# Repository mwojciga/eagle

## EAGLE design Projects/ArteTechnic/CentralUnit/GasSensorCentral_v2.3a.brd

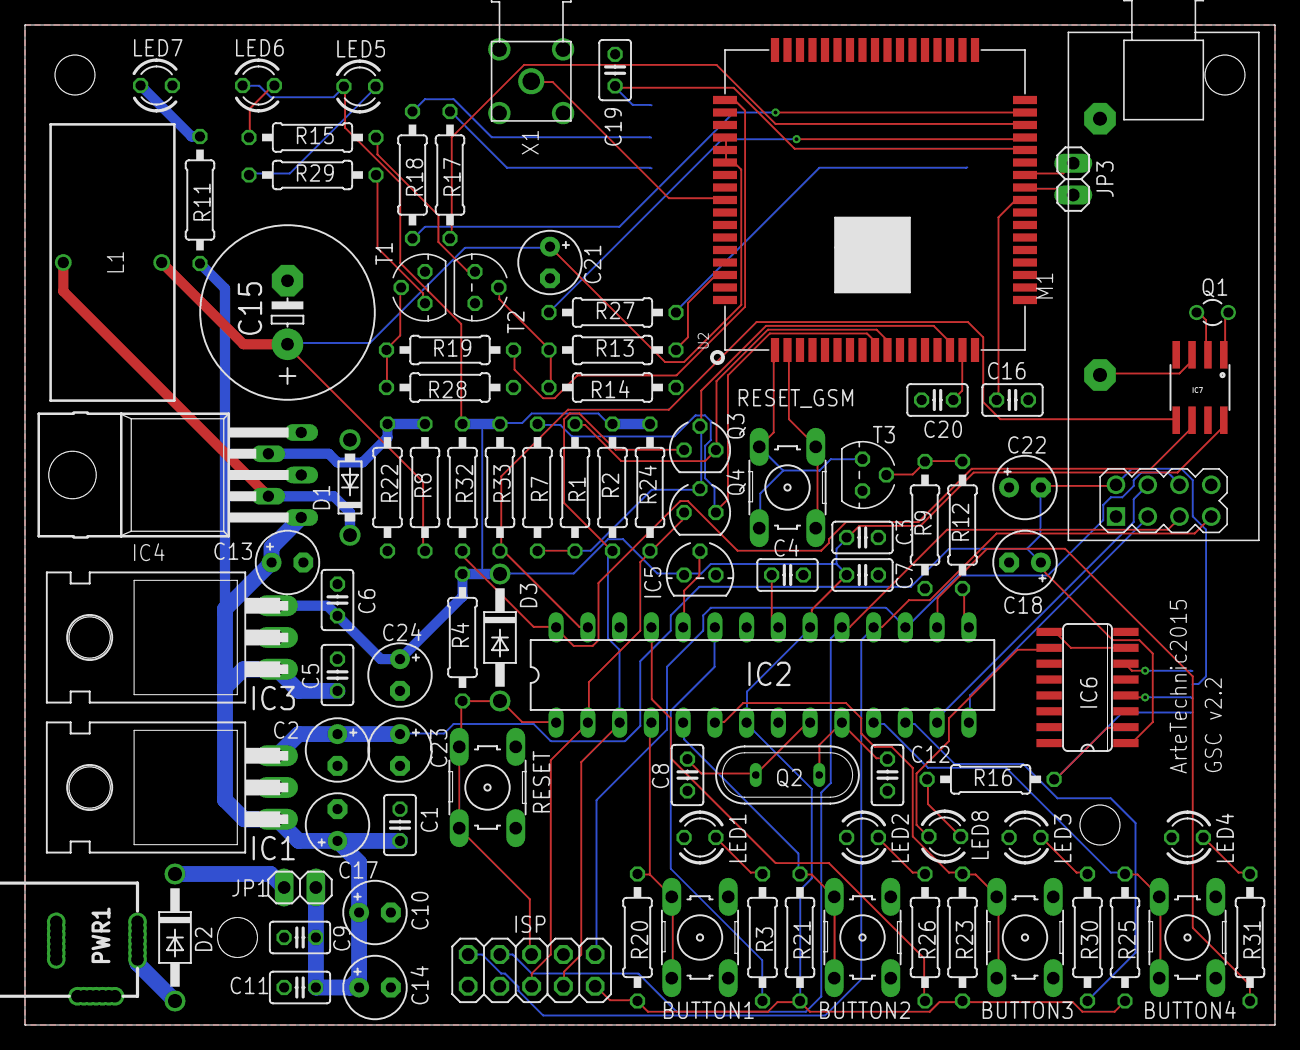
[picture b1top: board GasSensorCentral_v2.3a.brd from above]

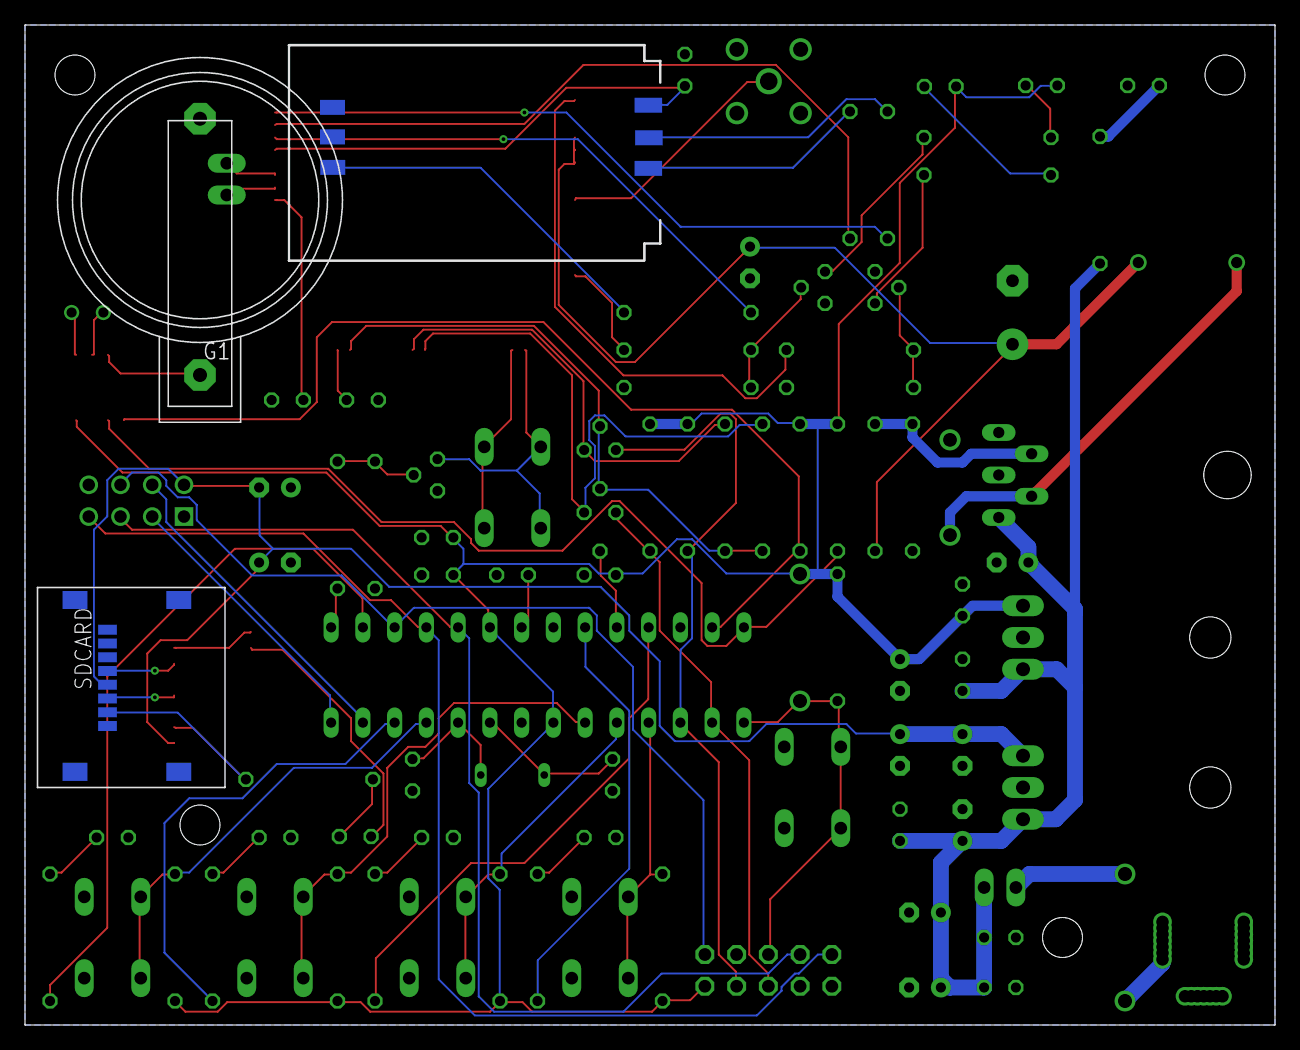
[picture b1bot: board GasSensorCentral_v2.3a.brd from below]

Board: 2 copper layers, 100.0 x 80.0 mm, 96 parts (3 on the bottom side), 72 nets.

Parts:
BUTTON1, BUTTON2, BUTTON3, BUTTON4: B3F-10XX
C1, C3, C4, C6, C7, C9, C11, C19, C20: 100nF; C025-025X050
C2: 2.2uF; E2,5-5
C5: 330nF; C025-025X050
C8, C12: 22pF; C025-025X050
C10, C17, C22, C23, C24: 1uF; E2,5-5
C13, C21: 100uF; E2,5-5
C14: 4.7uF; E2,5-5
C15: 3300uF; E5-13
C16: 4.7uF; C025-025X050
C18: 10uF; E2,5-5
D1: 1N5823; DO41-7.6
D2, D3: 1N4001; DO41-10
G1: CR2032H
IC1: LF33CV; TO220H
IC2: MEGA8-P; DIL28-3
IC3: 7805T; TO220H
IC4: LM2576H; TO220-52
IC5: LM35CZ; TO92
IC6: 4050D; SO16
IC7: DS1307SO8; SO08
ISP: 2X05
JP1, JP3: 1X02
L1: 68uH; TJ4-U1
LED1, LED2, LED3, LED4: White; LED3MM
LED5, LED6, LED7: Blue; LED3MM
LED8: Yellow; LED3MM
M1: NRF24L01; WIRELESS-NRD24L01-PA-EXT
PWR1: PWR_JACK_UNI_MILLING
Q1: 32.768K-20PPM; TC26V
Q2: QS
Q3, Q4: BS170; SOT54E
R1, R2, R7, R11, R20, R21, R23, R24, R25, R32, R33: 10k; 0207/10
R3, R15, R26, R29, R30, R31: 330; 0207/10
R4: 22k; 0207/10
R8: 3.6k; 0207/10
R9, R14, R28: 47k; 0207/10
R12, R13, R19: 4.7k; 0207/10
R16: 1k; 0207/10
R17, R18, R27: 22R; 0207/10
R22: 1.5k; 0207/10
RESET: B3F-10XX
RESET_GSM: B3F-10XX
SDCARD: MX-47219-2001
SIMHOLDER: SIMHOLDER3
T1, T2, T3: BC547; TO92
U2: SIM900
X1: BU-SMA-G

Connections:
3V3: C2.+, C18.+, C22.-, C23.+, IC1.3, IC6.1, M1.2, SDCARD.4
5V0: C3.1, C6.1, C7.1, C24.+, D3.C, IC2.7, IC2.20, IC3.3, IC5.1, IC7.8, ISP.2, LED5.A, LED6.A, R2.2, R4.2, R20.2, R21.2, R23.2, R24.2, R25.2, R32.1, R33.1
BUTTON1: BUTTON1.3, BUTTON1.4, IC2.4, R20.1
BUTTON2: BUTTON2.3, BUTTON2.4, IC2.5, R21.1
BUTTON3: BUTTON3.3, BUTTON3.4, IC2.6, R23.1
BUTTON4: BUTTON4.3, BUTTON4.4, IC2.11, R25.1
CE: IC2.14, M1.3
CSN: IC2.13, M1.4
DBG_RXD: JP3.2, U2.28
DBG_TXD: JP3.1, U2.27
GND: BUTTON1.1, BUTTON1.2, BUTTON2.1, BUTTON2.2, BUTTON3.1, BUTTON3.2, BUTTON4.1, BUTTON4.2, C1.2, C2.-, C3.2, C4.2, C5.2, C6.2, C7.2, C8.1, C9.1, C10.-, C11.1, C12.1, C13.-, C14.-, C15.-, C16.1, C17.-, C18.-, C19.2, C20.1, C21.-, C22.+, C23.-, C24.-, D1.A, G1.-, IC1.2, IC2.8, IC2.22, IC3.2, IC4.3, IC4.5, IC5.3, IC6.8, IC6.11, IC6.14, IC7.4, ISP.3, ISP.8, ISP.10, LED1.K, LED2.K, LED3.K, LED4.K, LED7.K, M1.1, PWR1.-, PWR1.--, R9.1, R14.1, R22.2, R28.1, RESET.1, RESET.2, SDCARD.6, SDCARD.G1, SDCARD.G2, SDCARD.G3, SDCARD.G4, SIMHOLDER.6, T1.1, T2.1, T3.1, U2.17, U2.18, U2.29, U2.39, U2.45, U2.46, U2.53, U2.54, U2.58, U2.59, U2.61, U2.62, U2.63, U2.64, U2.65, X1.2, X1.3, X1.4, X1.5
LED1: IC2.23, R3.2
LED2: IC2.25, R26.2
LED3: IC2.12, R30.2
LED4: IC2.16, R31.2
LRXD: Q3.S, R1.1, U2.10
LTXD: Q4.S, R7.1, U2.9
MISO: IC2.18, ISP.9, M1.7
MOSI: IC2.17, ISP.1, M1.6
unnamed: C4.1, IC2.21
unnamed: IC7.2, Q1.1
unnamed: IC4.4, R8.2, R22.1
unnamed: D2.A, PWR1.+
unnamed: LED1.A, R3.1
unnamed: R27.2, SIMHOLDER.4
unnamed: LED5.K, R29.1
unnamed: IC7.1, Q1.2
unnamed: R13.1, R14.2, T2.2
unnamed: LED7.A, R11.1
unnamed: LED6.K, R15.1
unnamed: D1.C, IC4.2, L1.1
unnamed: C20.2, U2.16
unnamed: R9.2, R12.2, T3.2
unnamed: R19.1, R28.2, T1.2
unnamed: G1.+, IC7.3
unnamed: C16.2, U2.26
unnamed: LED2.A, R26.1
unnamed: LED3.A, R30.1
unnamed: LED4.A, R31.1
unnamed: R18.1, SIMHOLDER.2
unnamed: R17.1, SIMHOLDER.3
unnamed: IC6.2, R16.2, SDCARD.2
unnamed: IC6.4, SDCARD.3
unnamed: C8.2, IC2.9, Q2.1
unnamed: IC6.6, SDCARD.5
unnamed: IC6.10, LED8.A
unnamed: LED8.K, R16.1
unnamed: C12.2, IC2.10, Q2.2
NETLIGHT: R19.2, U2.52
NETLIGHT_INFO: R29.2, T1.3
PWRKEY: RESET_GSM.3, RESET_GSM.4, T3.3, U2.1
PWRKEY_OUT: RESET_GSM.1, RESET_GSM.2, U2.2
RESET: D3.A, IC2.1, ISP.5, R4.1, RESET.3, RESET.4
RF_ANT: U2.60, X1.1
RXD: IC2.2, ISP.6, Q4.D, R24.1
SCK: IC2.19, ISP.7, M1.5
SCL: IC2.28, IC7.6, R32.2
SCLK: IC6.7, IC6.9
SDA: IC2.27, IC7.5, R33.2
SIM_CLK: R17.2, U2.32
SIM_DATA: R27.1, U2.31
SIM_RST: R18.2, U2.33
SIM_VDD: C19.1, SIMHOLDER.1, U2.30
SOFTRESET: IC2.15, R12.1
STATUS: R13.2, U2.66
STATUS_INFO: R15.2, T2.3
TEMP: IC2.24, IC5.2
TXD: IC2.3, ISP.4, Q3.D, R2.1
VBAT: C15.+, C21.+, L1.2, R8.1, U2.55, U2.56, U2.57
VDD_EXT: Q3.G, Q4.G, R1.2, R7.2, U2.15
VIN_BUTTON: C1.1, C5.1, C9.2, C10.+, C11.2, C13.+, C14.+, C17.+, IC1.1, IC3.1, IC4.1, JP1.2, R11.2
VIN_JACK: D2.C, JP1.1

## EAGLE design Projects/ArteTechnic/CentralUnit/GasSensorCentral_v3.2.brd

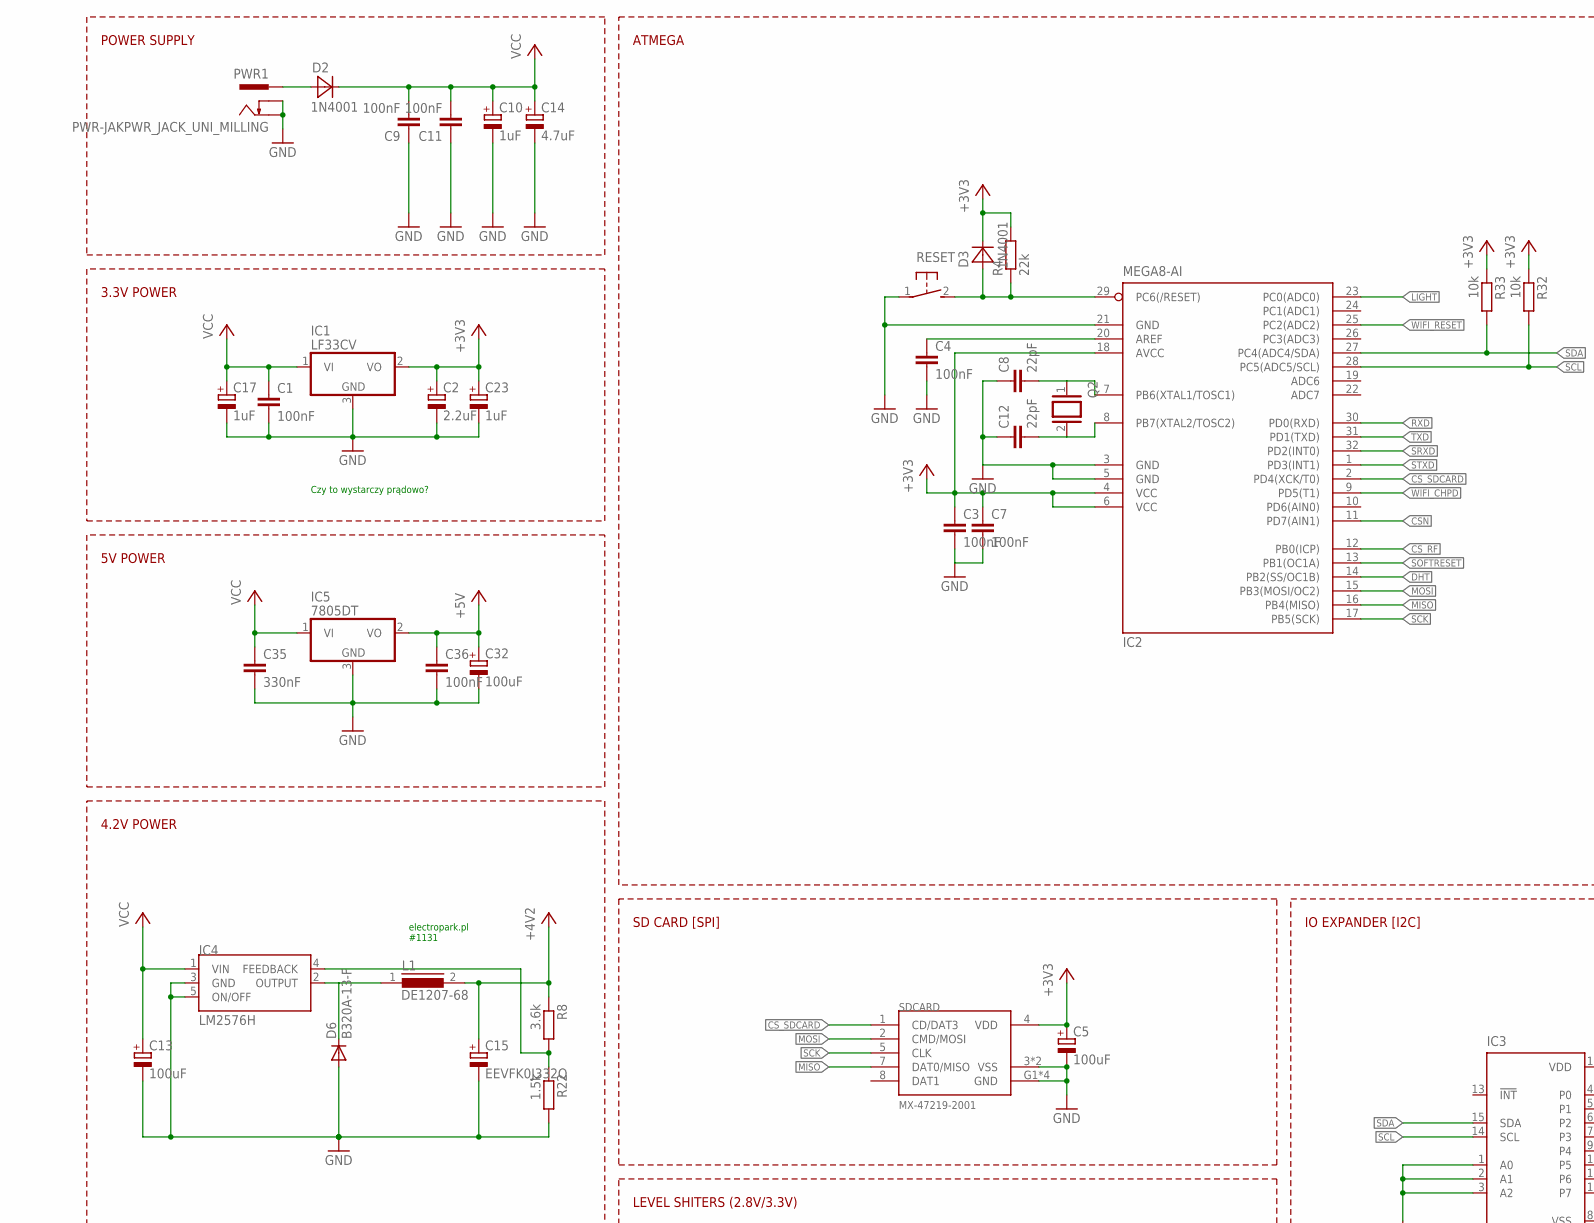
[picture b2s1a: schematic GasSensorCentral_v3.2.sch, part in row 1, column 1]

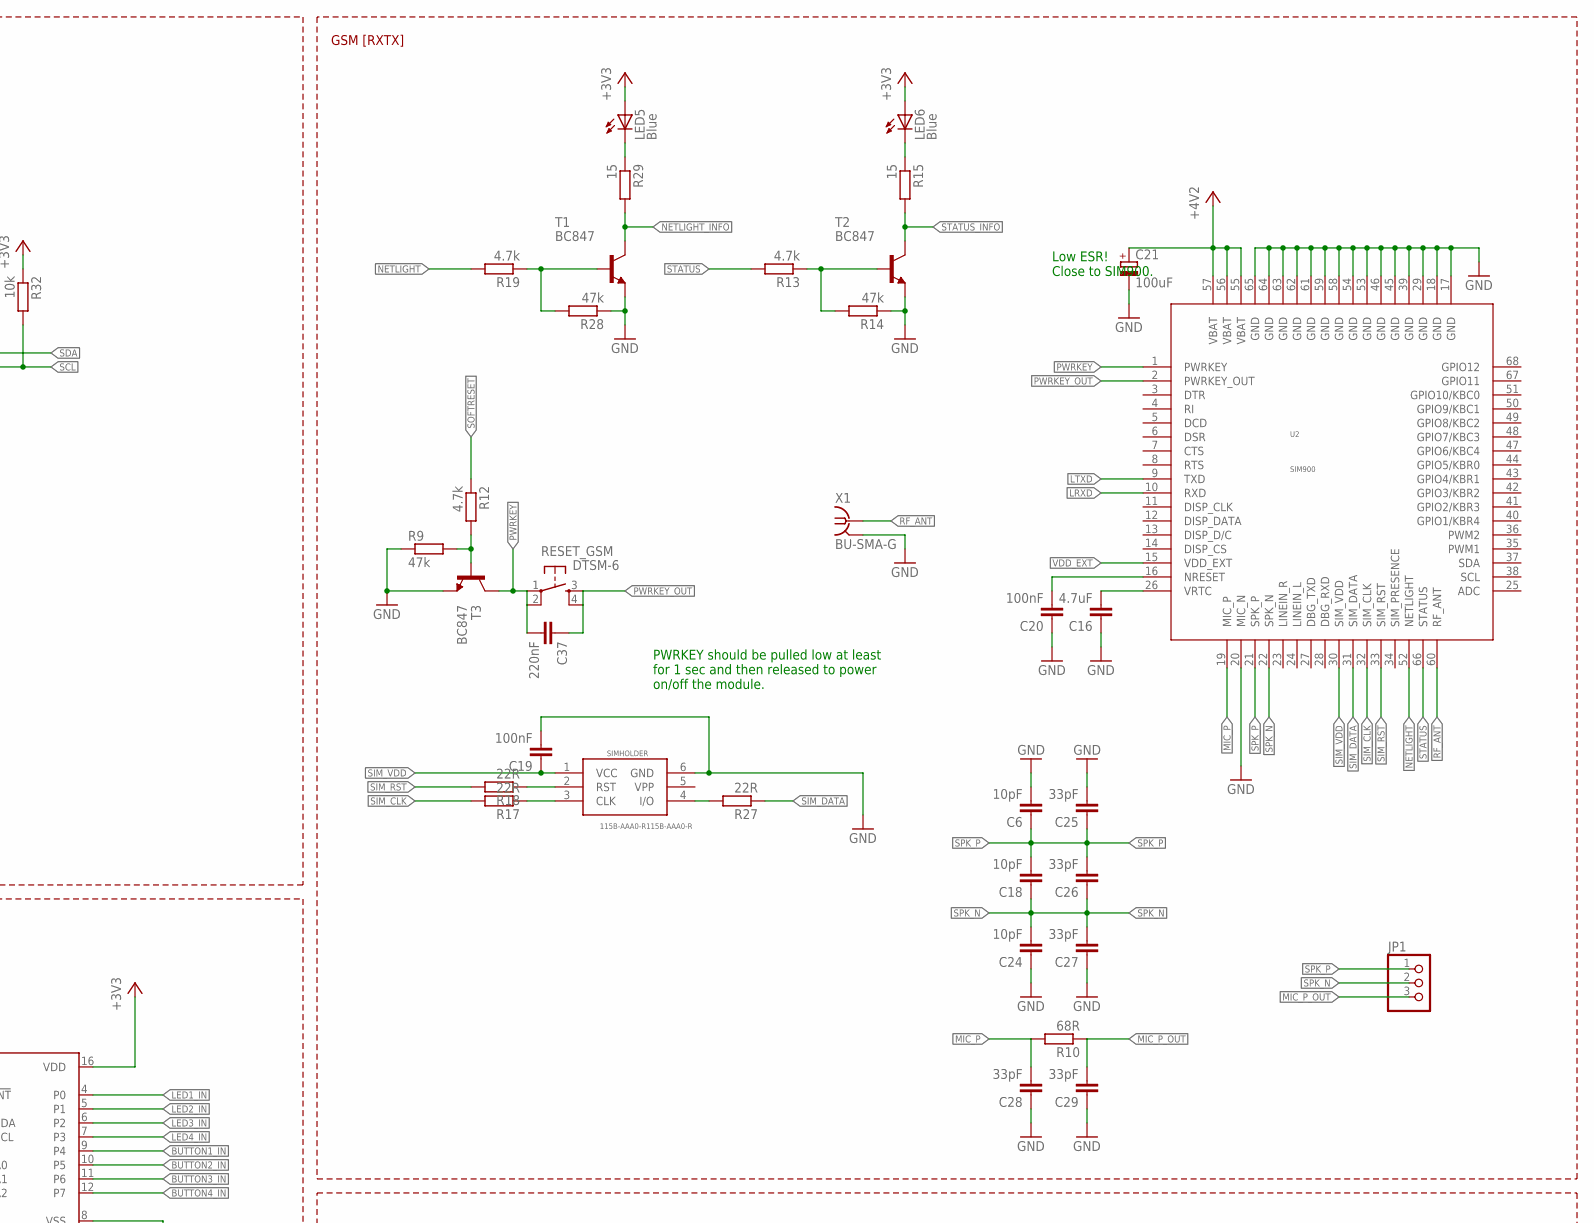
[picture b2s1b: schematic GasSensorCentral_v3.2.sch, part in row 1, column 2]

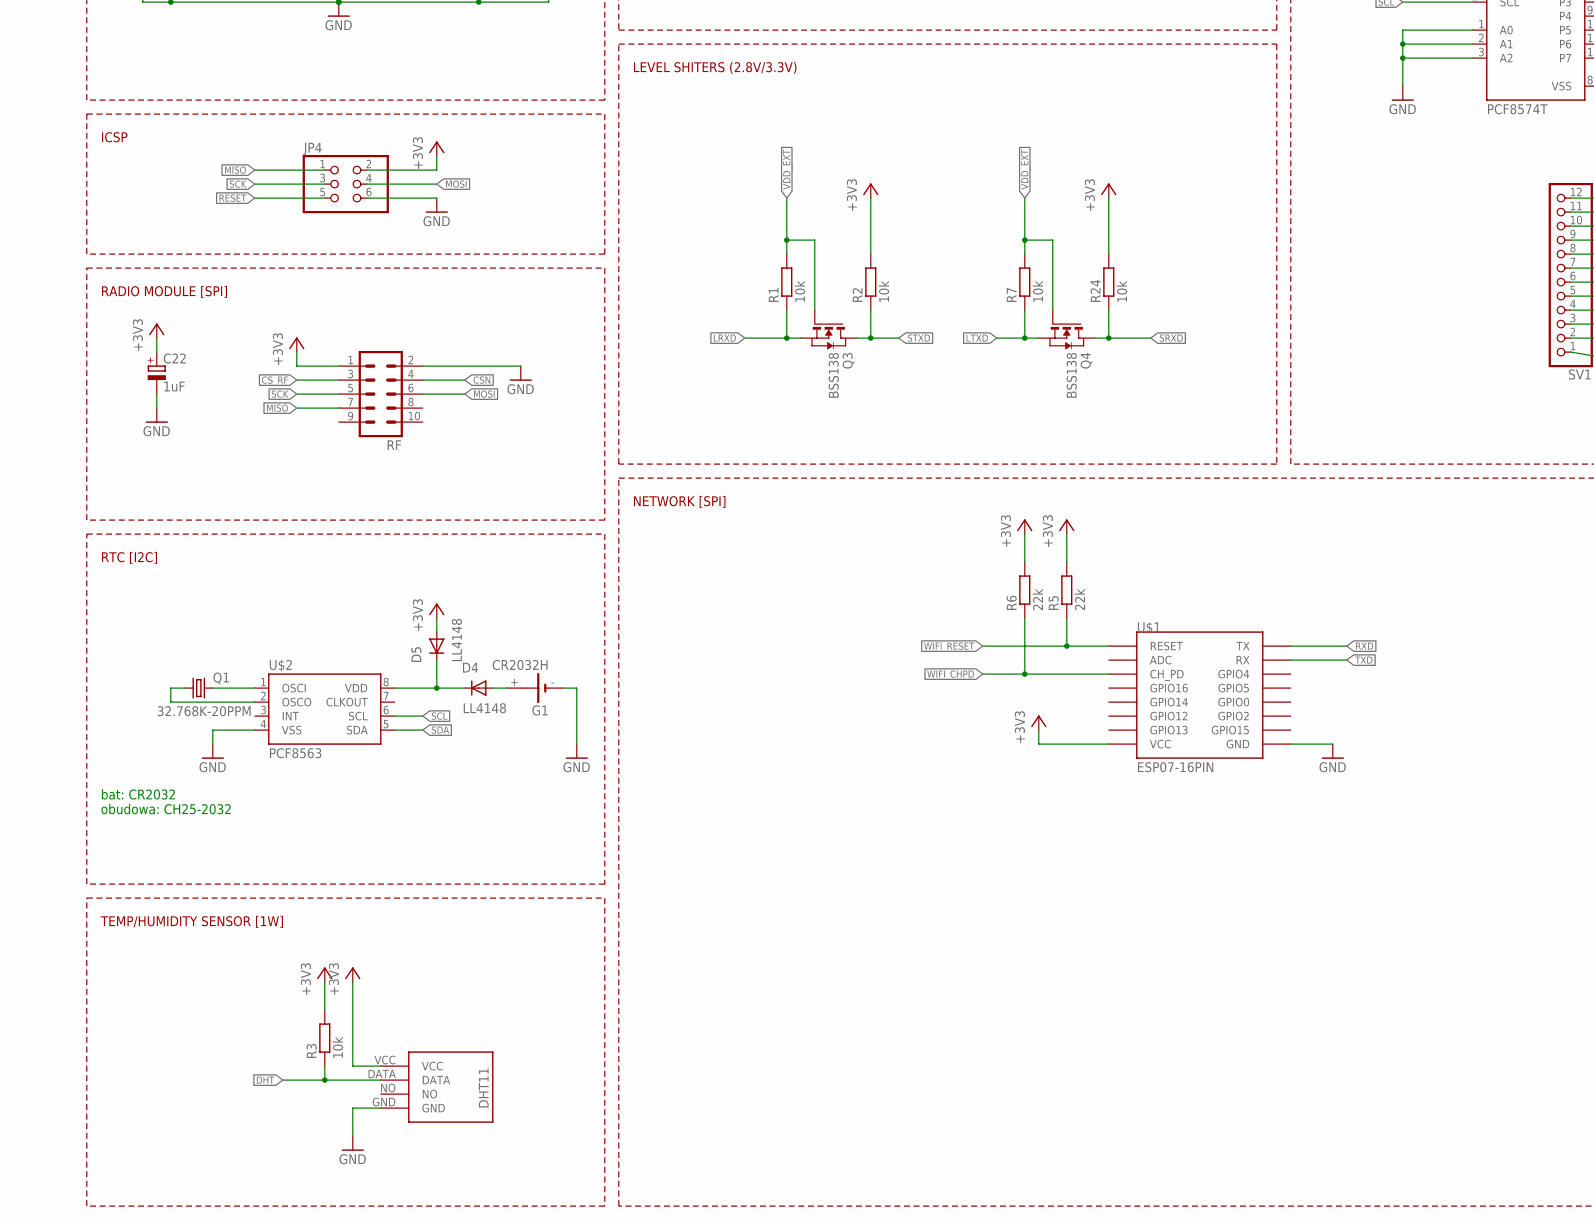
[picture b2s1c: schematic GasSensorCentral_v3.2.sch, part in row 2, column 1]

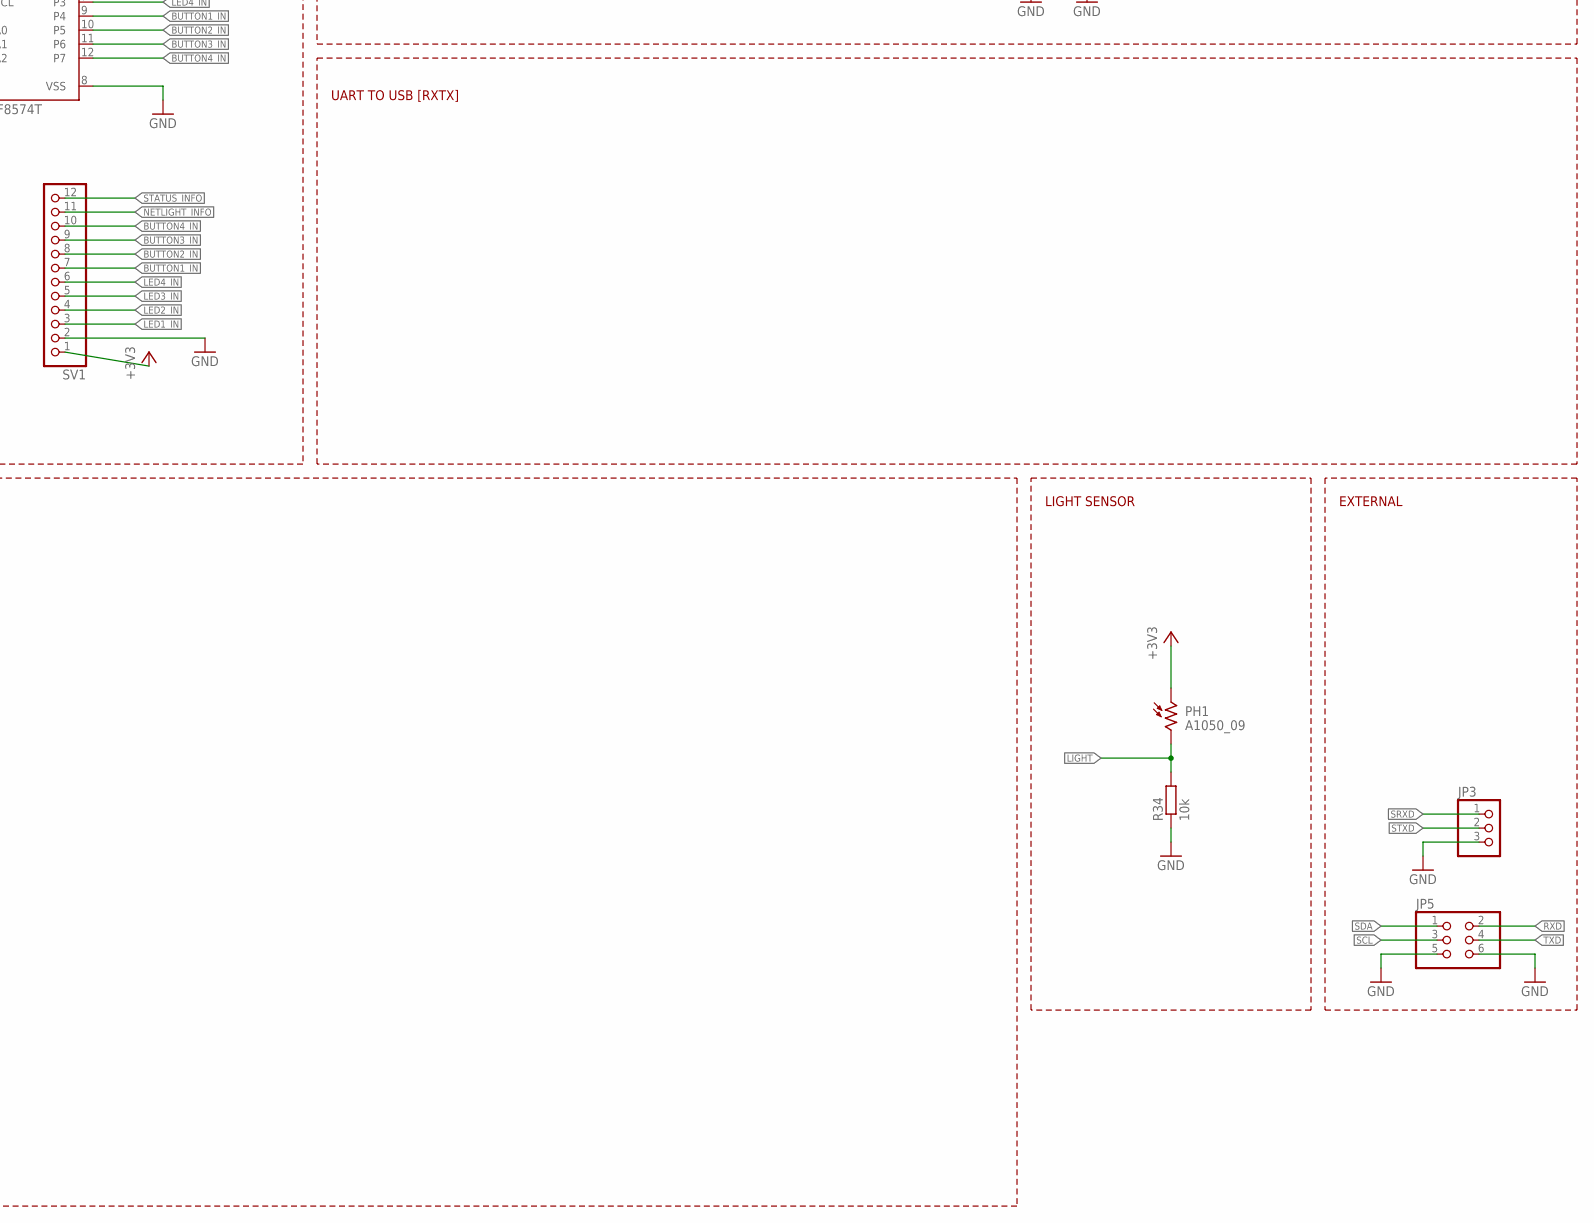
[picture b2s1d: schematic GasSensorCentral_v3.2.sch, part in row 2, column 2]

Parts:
C1, C3, C4, C7, C9, C11, C19, C20, C36: 100nF; C0805
C2: 2.2uF; PANASONIC_B
C5, C13, C21, C32: 100uF; PANASONIC_B
C6, C18, C24: 10pF; C0805
C8, C12: 22pF; C0805
C10, C17, C22, C23: 1uF; PANASONIC_B
C14: 4.7uF; PANASONIC_B
C15: EEVFK0J332Q; 153CLV-1212
C16: 4.7uF; C0805
C25, C26, C27, C28, C29: 33pF; C0805
C35: 330nF; C0805
C37: 220nF; C0805
D2, D3: 1N4001; SMA
D4, D5: LL4148; SOD80C
D6: B320A-13-F; DO214AC
G1: CR2032H
IC1: LF33CV; TO252
IC2: MEGA8-AI; TQFP32-08
IC3: PCF8574T; SO16W
IC4: LM2576H; TO220-52
IC5: 7805DT; TO252
JP1: PINHD-1X3/90; 1X03/90
JP3: PINHD-1X3; 1X03
JP4, JP5: PINHD-2X3; 2X03
L1: DE1207-68; DE1207
LED5, LED6: Blue; SML0805
PH1: A1050_09; T0-46-A10XX
PWR1: PWR-JAKPWR_JACK_UNI_MILLING; PWR_JACK_UNI_MILLING
Q1: 32.768K-20PPM; TC26V
Q2: XTAL/S; QS
Q3, Q4: BSS138; SOT-23
R1, R2, R3, R7, R24, R32, R33, R34: 10k; R0805
R4, R5, R6: 22k; R0805
R8: 3.6k; R0805
R9, R14, R28: 47k; R0805
R10: 68R; R0805
R12, R13, R19: 4.7k; R0805
R15, R29: 15; R0805
R17, R18, R27: 22R; R0805
R22: 1.5k; R0805
RESET: 31-XX; B3F-31XX
RESET_GSM: DTSM-6
RF: ML10
SDCARD: MX-47219-2001
SIMHOLDER: 115B-AAA0-R115B-AAA0-R; 115B-AAA0-R
SV1: PINHD-1X12; 1X12
T1, T2, T3: BC847; SOT23
U2: SIM900
U$1: ESP07-16PIN
U$2: PCF8563; SO08
U$3: DHT11-PION.
X1: BU-SMA-G

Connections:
+3V3: C2.+, C3.1, C5.+, C7.1, C22.+, C23.+, D3.C, D5.A, IC1.2 (VO), IC2.4 (VCC), IC2.6 (VCC), IC2.18 (AVCC), IC3.16 (VDD), JP4.2, LED5.A, LED6.A, PH1.1, R2.2, R3.2, R4.2, R5.2, R6.2, R24.2, R32.1, R33.1, RF.1, SDCARD.4 (VDD), SV1.1, U$1.VCC, U$3.VCC
+4V2: C15.+, C21.+, L1.2, R8.1, U2.55 (VBAT), U2.56 (VBAT), U2.57 (VBAT)
+5V: C32.+, C36.1, IC5.2 (VO)
BUTTON1_IN: IC3.9 (P4), SV1.7
BUTTON2_IN: IC3.10 (P5), SV1.8
BUTTON3_IN: IC3.11 (P6), SV1.9
BUTTON4_IN: IC3.12 (P7), SV1.10
CSN: IC2.11 (PD7(AIN1)), RF.4
CS_RF: IC2.12 (PB0(ICP)), RF.3
CS_SDCARD: IC2.2 (PD4(XCK/T0)), SDCARD.1 (CD/DAT3)
DHT: IC2.14 (PB2(SS/OC1B)), R3.1, U$3.DATA
GND: C1.2, C2.-, C3.2, C4.2, C5.-, C6.2, C7.2, C8.1, C9.1, C10.-, C11.1, C12.1, C13.-, C14.-, C15.-, C16.1, C17.-, C19.2, C20.1, C21.-, C22.-, C23.-, C24.1, C25.2, C27.1, C28.1, C29.1, C32.-, C35.2, C36.2, G1.-, IC1.3 (GND), IC2.3 (GND), IC2.5 (GND), IC2.21 (GND), IC3.1 (A0), IC3.2 (A1), IC3.3 (A2), IC3.8 (VSS), IC4.3 (GND), IC4.5 (ON/OFF), IC5.3 (GND), JP3.3, JP4.6, JP5.5, JP5.6, PWR1.-, PWR1.-1 (-), PWR1.-2 (-), PWR1.-3 (-), PWR1.-4 (-), PWR1.-5 (-), PWR1.-6 (-), PWR1.--, PWR1.--1 (--), PWR1.--2 (--), PWR1.--3 (--), PWR1.--4 (--), PWR1.--5 (--), PWR1.--6 (--), R9.1, R14.1, R22.2, R28.1, R34.1, RESET.1, RF.2, SDCARD.3 (VSS), SDCARD.6 (VSS), SDCARD.G1 (GND), SDCARD.G2 (GND), SDCARD.G3 (GND), SDCARD.G4 (GND), SIMHOLDER.6 (GND), SV1.2, T1.2 (E), T2.2 (E), T3.2 (E), U2.17 (GND), U2.18 (GND), U2.20 (MIC_N), U2.29 (GND), U2.39 (GND), U2.45 (GND), U2.46 (GND), U2.53 (GND), U2.54 (GND), U2.58 (GND), U2.59 (GND), U2.61 (GND), U2.62 (GND), U2.63 (GND), U2.64 (GND), U2.65 (GND), U$1.GND, U$2.4 (VSS), U$3.GND, X1.2, X1.3 (2), X1.4 (2), X1.5 (2)
LED1_IN: IC3.4 (P0), SV1.3
LED2_IN: IC3.5 (P1), SV1.4
LED3_IN: IC3.6 (P2), SV1.5
LED4_IN: IC3.7 (P3), SV1.6
LIGHT: IC2.23 (PC0(ADC0)), PH1.2, R34.2
LRXD: Q3.2 (S), R1.1, U2.10 (RXD)
LTXD: Q4.2 (S), R7.1, U2.9 (TXD)
MIC_P: C28.2, R10.2, U2.19 (MIC_P)
MIC_P_OUT: C29.2, JP1.3, R10.1
MISO: IC2.16 (PB4(MISO)), JP4.1, RF.7, SDCARD.7 (DAT0/MISO)
MOSI: IC2.15 (PB3(MOSI/OC2)), JP4.4, RF.6, SDCARD.2 (CMD/MOSI)
unnamed: C4.1, IC2.20 (AREF)
unnamed: Q1.1, U$2.2 (OSCO)
unnamed: IC4.4 (FEEDBACK), R8.2, R22.1
unnamed: D2.A, PWR1.+, PWR1.+1 (+), PWR1.+2 (+), PWR1.+3 (+), PWR1.+4 (+), PWR1.+5 (+), PWR1.+6 (+)
unnamed: D4.C, D5.C, U$2.8 (VDD)
unnamed: R27.2, SIMHOLDER.4 (I/O)
unnamed: LED5.C, R29.1
unnamed: Q1.2, U$2.1 (OSCI)
unnamed: R13.1, R14.2, T2.1 (B)
unnamed: LED6.C, R15.1
unnamed: D6.C, IC4.2 (OUTPUT), L1.1
unnamed: C20.2, U2.16 (NRESET)
unnamed: R9.2, R12.2, T3.1 (B)
unnamed: R19.1, R28.2, T1.1 (B)
unnamed: D4.A, G1.+
unnamed: C16.2, U2.26 (VRTC)
unnamed: R18.1, SIMHOLDER.2 (RST)
unnamed: R17.1, SIMHOLDER.3 (CLK)
unnamed: C8.2, IC2.7 (PB6(XTAL1/TOSC1)), Q2.1
unnamed: C12.2, IC2.8 (PB7(XTAL2/TOSC2)), Q2.2
NETLIGHT: R19.2, U2.52 (NETLIGHT)
NETLIGHT_INFO: R29.2, SV1.11, T1.3 (C)
PWRKEY: C37.2, RESET_GSM.1, RESET_GSM.2, T3.3 (C), U2.1 (PWRKEY)
PWRKEY_OUT: C37.1, RESET_GSM.3, RESET_GSM.4, U2.2 (PWRKEY_OUT)
RESET: D3.A, IC2.29 (PC6(/RESET)), JP4.5, R4.1, RESET.2 (S)
RF_ANT: U2.60 (RF_ANT), X1.1
RXD: IC2.30 (PD0(RXD)), JP5.2, U$1.TX
SCK: IC2.17 (PB5(SCK)), JP4.3, RF.5, SDCARD.5 (CLK)
SCL: IC2.28 (PC5(ADC5/SCL)), IC3.14 (SCL), JP5.3, R32.2, U$2.6 (SCL)
SDA: IC2.27 (PC4(ADC4/SDA)), IC3.15 (SDA), JP5.1, R33.2, U$2.5 (SDA)
SIM_CLK: R17.2, U2.32 (SIM_CLK)
SIM_DATA: R27.1, U2.31 (SIM_DATA)
SIM_RST: R18.2, U2.33 (SIM_RST)
SIM_VDD: C19.1, SIMHOLDER.1 (VCC), U2.30 (SIM_VDD)
SOFTRESET: IC2.13 (PB1(OC1A)), R12.1
SPK_N: C18.1, C24.2, C26.1, C27.2, JP1.2, U2.22 (SPK_N)
SPK_P: C6.1, C18.2, C25.1, C26.2, JP1.1, U2.21 (SPK_P)
SRXD: IC2.32 (PD2(INT0)), JP3.1, Q4.1 (D), R24.1
STATUS: R13.2, U2.66 (STATUS)
STATUS_INFO: R15.2, SV1.12, T2.3 (C)
STXD: IC2.1 (PD3(INT1)), JP3.2, Q3.1 (D), R2.1
TXD: IC2.31 (PD1(TXD)), JP5.4, U$1.RX
VCC: C1.1, C9.2, C10.+, C11.2, C13.+, C14.+, C17.+, C35.1, D2.C, IC1.1 (VI), IC4.1 (VIN), IC5.1 (VI)
VDD_EXT: Q3.3 (G), Q4.3 (G), R1.2, R7.2, U2.15 (VDD_EXT)
WIFI_CHPD: IC2.9 (PD5(T1)), R6.1, U$1.CH_PD
WIFI_RESET: IC2.25 (PC2(ADC2)), R5.1, U$1.REST (RESET)

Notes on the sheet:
PWRKEY should be pulled low at least for 1 sec and then released to power on/off the module.
Low ESR! Close to SIM900.
bat: CR2032 obudowa: CH25-2032
POWER SUPPLY
3.3V POWER
ICSP
4.2V POWER
RADIO MODULE [SPI]
LEVEL SHITERS (2.8V/3.3V)
ATMEGA
SD CARD [SPI]
RTC [I2C]
GSM [RXTX]
NETWORK [SPI]
IO EXPANDER [I2C]
TEMP/HUMIDITY SENSOR [1W]
electropark.pl #1131
UART TO USB [RXTX]
LIGHT SENSOR
EXTERNAL
5V POWER
Czy to wystarczy prądowo?

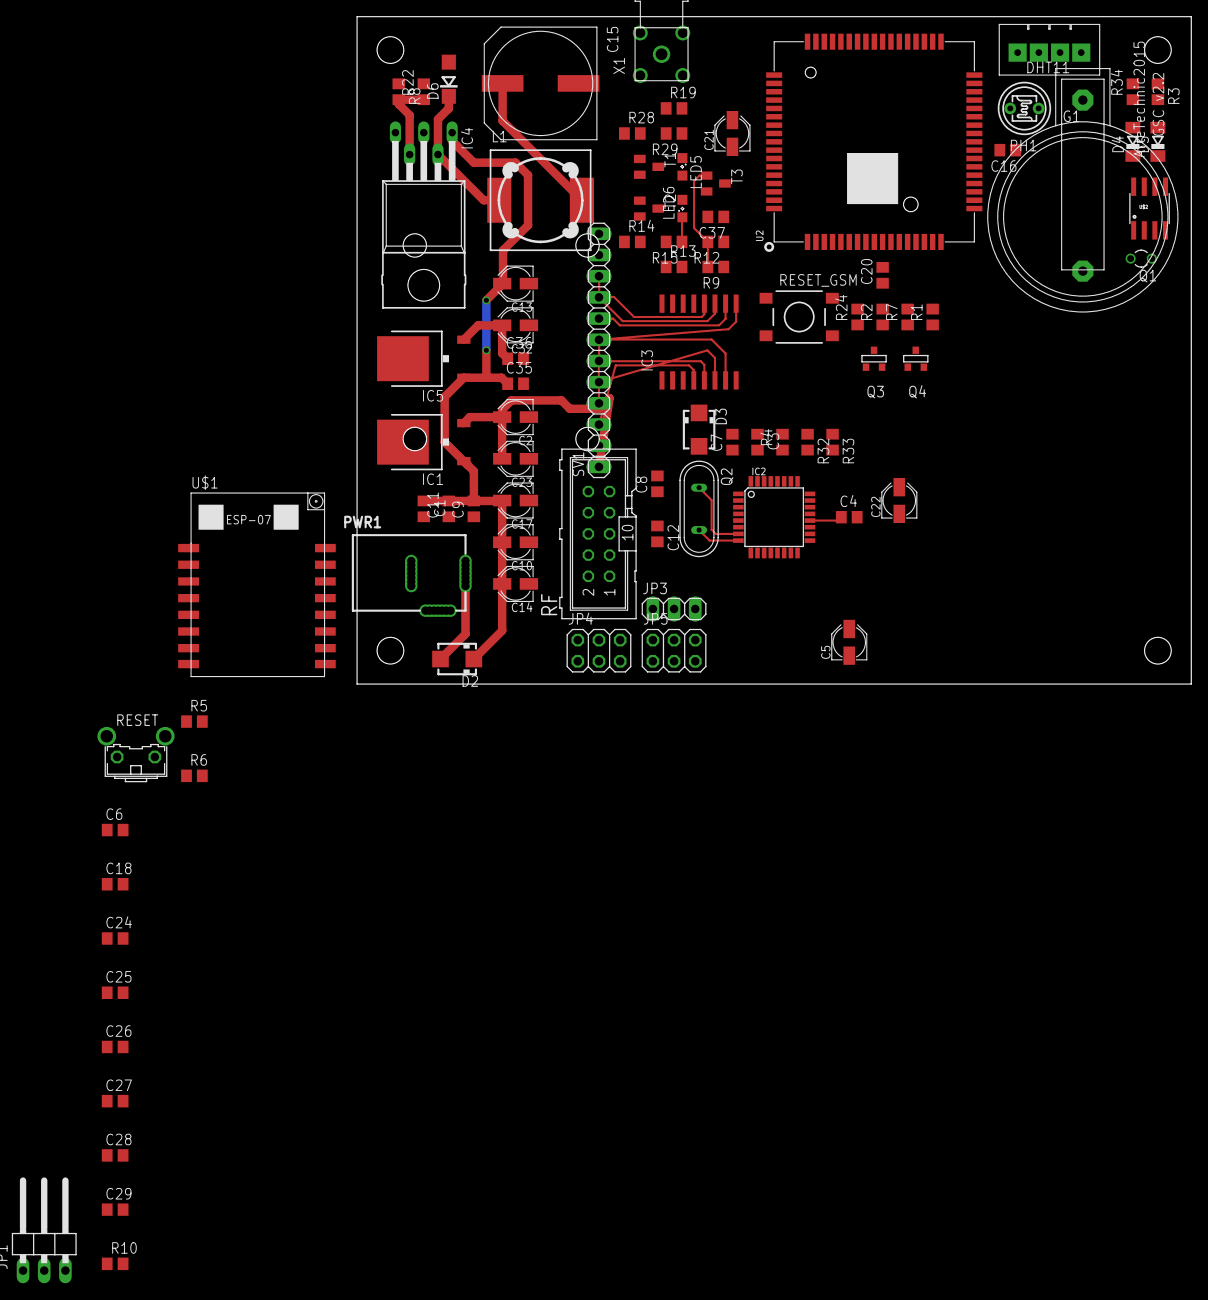
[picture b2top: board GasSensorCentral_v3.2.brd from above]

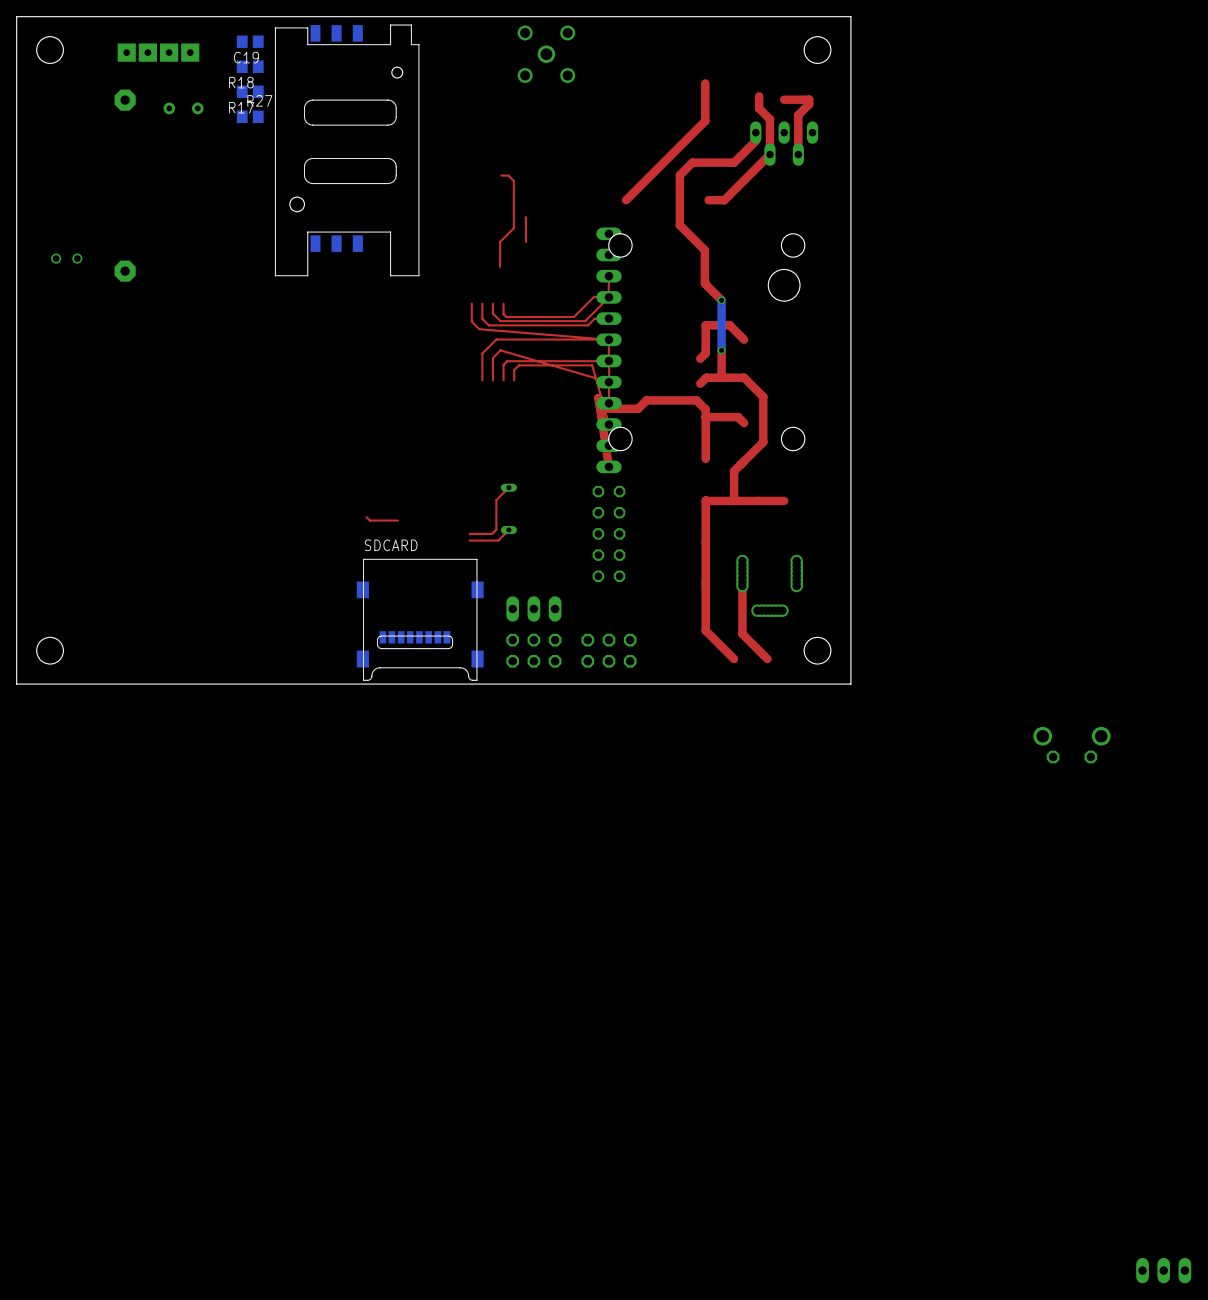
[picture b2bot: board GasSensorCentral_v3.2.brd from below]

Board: 2 copper layers, 100.0 x 80.0 mm, 96 parts (6 on the bottom side), 69 nets.

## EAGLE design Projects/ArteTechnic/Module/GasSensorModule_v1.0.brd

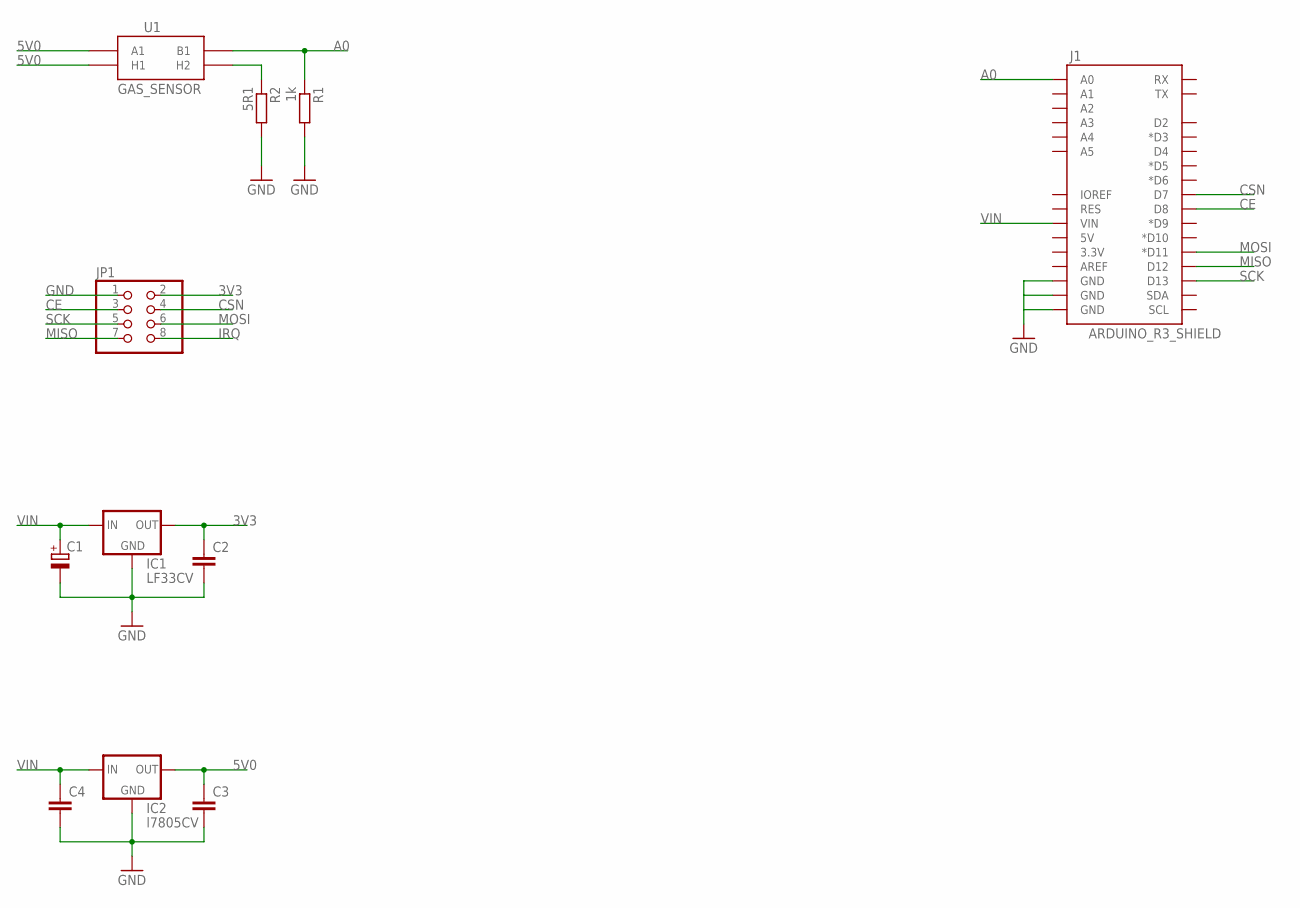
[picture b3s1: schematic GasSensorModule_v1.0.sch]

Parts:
C1: CPOL-EUE2,5-6E; E2,5-6E
C2, C3, C4: C-EU025-025X050; C025-025X050
IC1: LF33CV; 78XXS
IC2: l7805CV; 78XXS
J1: ARDUINO_R3_SHIELD; UNO_R3_SHIELD
JP1: PINHD-2X4; 2X04
R1: 1k; 0207/10
R2: 5R1; 0207/10
U1: GAS_SENSOR; MQ-3

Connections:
3V3: C2.1, IC1.OUT, JP1.2
5V0: C3.1, IC2.OUT, U1.A1, U1.HA (H1)
A0: J1.A0, R1.1, U1.B1
CE: J1.D8, JP1.3
CSN: J1.D7, JP1.4
GND: C1.-, C2.2, C3.2, C4.2, IC1.GND, IC2.GND, J1.GND@0 (GND), J1.GND@1 (GND), J1.GND@2 (GND), JP1.1, R1.2, R2.2
IRQ: JP1.8
MISO: J1.D12, JP1.7
MOSI: J1.D11 (*D11), JP1.6
unnamed: R2.1, U1.HB (H2)
SCK: J1.D13, JP1.5
VIN: C1.+, C4.1, IC1.IN, IC2.IN, J1.VIN

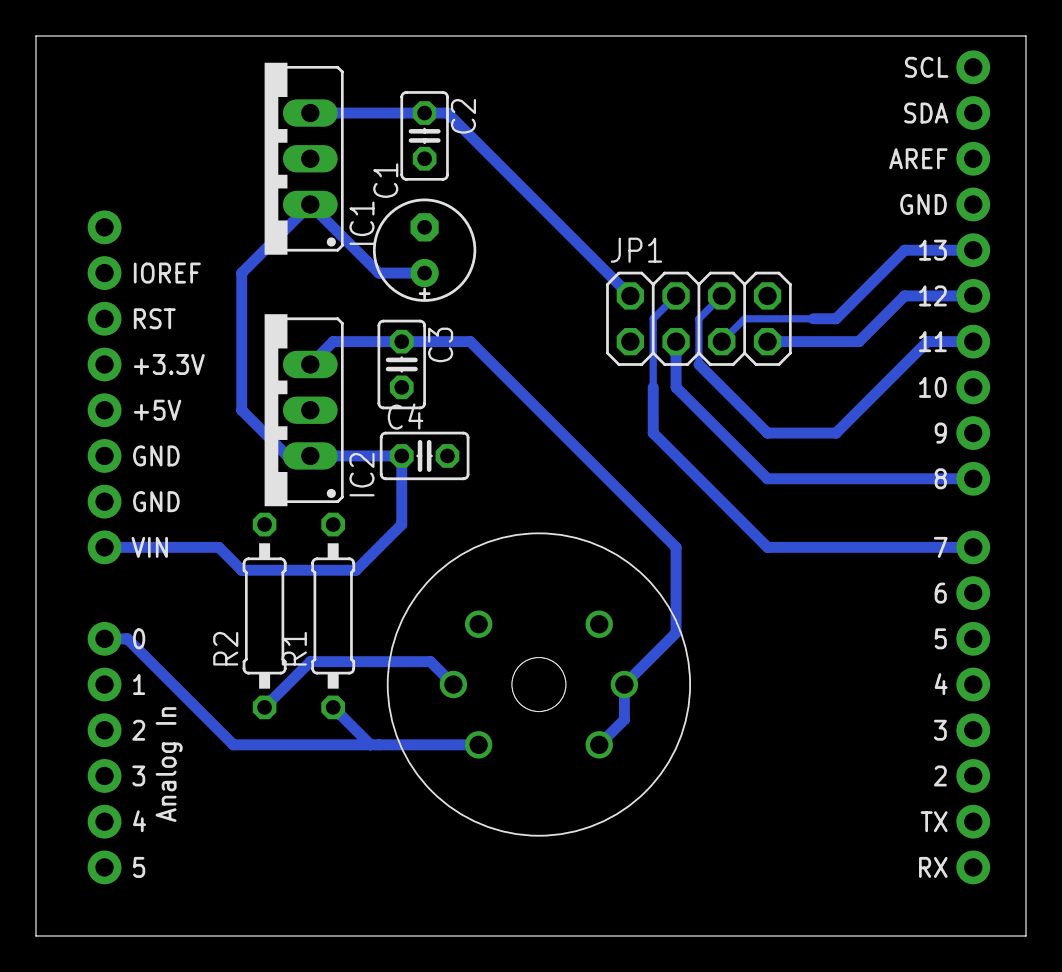
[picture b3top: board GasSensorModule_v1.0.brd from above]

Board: 2 copper layers, 55.0 x 50.0 mm, 11 parts (0 on the bottom side), 11 nets.

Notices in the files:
parts and their libraries:
diy-modules: Released under the Creative Commons Attribution 4.0 International License: http://creativecommons.org/licenses/by/4.0
SparkFun-FreqCtrl: Licensing: Creative Commons ShareAlike 4.0 International - https://creativecommons.org/licenses/by-sa/4.0
